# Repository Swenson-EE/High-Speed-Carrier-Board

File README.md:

# LattePanda-Mu High-Speed Carrier Board

A custom carrier board designed for the **LattePanda Mu** compute module, with a focus on high-speed digital design, signal integrity, power distribution, and practical PCB design.

This project was developed to apply high-speed PCB design concepts to a real embedded computing platform. The design process incorporated concepts studied through online courses, technical forums, datasheets, and reference designs.

> **Project Status:** Fabrication
> **PCB Design Tool:** KiCad
> **Primary Focus:** High-speed digital design, power distribution, signal integrity, and embedded hardware

---

## Overview

The goal of this project is to design a custom carrier board around the LattePanda Mu rather than relying on an off-the-shelf carrier board to explore high-speed digital design concepts.

The carrier board is intended to provide practical interfaces for development and experimentation while giving me experience designing a PCB containing multiple high-speed interfaces.

### Design Goals

- Develop a custom carrier board for the LattePanda Mu
- Apply high-speed PCB layout techniques
- Develop controlled-impedance routing practices
- Maintain appropriate differential-pair geometry
- Minimize high-speed signal discontinuities
- Develop a robust power distribution network
- Practice schematic-to-PCB design workflows
- Use datasheets and reference documentation to make design decisions
- Validate the design using available electrical and PCB design tools
- Produce a board suitable for fabrication and bring-up

---

## Hardware

### Compute Module

**LattePanda Mu**

The LattePanda Mu provides the primary compute platform for the carrier board.

The carrier board interfaces with the module through its high-density connectors and routes the available interfaces to the desired peripherals and connectors.

---

## PCB Designs

<table style="background: white;">
  <tr>
    <td align="center"><b>Top Silk Screen</b><br></td>
  </tr>
  <tr>
    <td align="center"><b>Front Cu (L1)</b><br></td>
  </tr>
  <tr>
    <td align="center"><b>GND (L2)</b><br></td>
  </tr>
  <tr>
    <td align="center"><b>PWR (L3)</b><br></td>
  </tr>
  <tr>
    <td align="center"><b>Bottom Cu (L4)</b><br></td>
  </tr>
</table>

## Interfaces

The carrier board is designed around several interfaces provided by the LattePanda Mu.

| Interface      | Purpose                     | Design Considerations                       |
| -------------- | --------------------------- | ------------------------------------------- |
| USB            | Peripheral connectivity     | High-speed differential routing             |
| HDMI / Display | Display output              | Differential high-speed routing             |
| Ethernet       | Network connectivity        | Differential pairs and magnetics            |
| PCIe           | Expansion                   | Controlled impedance / differential routing |
| M.2            | Expansion/storage           | High-speed differential routing             |
| GPIO           | General-purpose I/O         | Digital signal integrity                    |
| Power          | Module and peripheral power | Power integrity / decoupling                |

---

# High-Speed PCB Design

A major purpose of this project is to practice PCB design techniques applicable to high-speed digital hardware.

Rather than treating PCB traces simply as electrical connections, the design considers them as transmission lines at sufficiently high signal frequencies.

Areas being considered include:

### Controlled Impedance

High-speed interfaces are routed using appropriate controlled-impedance structures based on the PCB stackup and manufacturer's capabilities.

Examples include:

- Differential impedance
- Single-ended impedance
- Trace width
- Trace spacing
- Reference planes
- Dielectric thickness
- Copper thickness

The final trace geometries are based on the selected PCB stackup rather than relying solely on generic routing rules.

### Differential Pairs

High-speed differential interfaces are routed as matched differential pairs where required.

Design considerations include:

- Differential impedance
- Pair spacing
- Intra-pair length matching
- Continuous reference planes
- Avoiding unnecessary vias
- Minimizing discontinuities
- Maintaining consistent routing geometry

### Return Paths

High-speed signal routing considers the return current path rather than treating the signal trace independently.

Particular attention is given to:

- Continuous reference planes
- Plane transitions
- Ground vias
- Layer transitions
- Signal crossings
- Connector transitions

### Via Design

Vias can introduce discontinuities into high-speed signals.

Where applicable, the design considers:

- Via stubs
- Via placement
- Differential via geometry
- Ground-via placement
- Layer transitions
- Back-drilling requirements

---

# Power Distribution

The carrier board includes power regulation and distribution for the compute module and attached peripherals.

Power design considerations include:

- Input power requirements
- Voltage regulation
- Current requirements
- Decoupling
- Ground-plane design

Decoupling capacitors are placed with consideration for the physical connection between the capacitor, power pin, and return path rather than simply placing them near the associated component.

---

# PCB Stackup

The PCB stackup is an important part of the high-speed design.

The stackup is selected based on the requirements of the interfaces being routed and the capabilities of the intended PCB manufacturer.

Example stackup:

| Layer | Function |
| ----- | -------- |
| L1    | Signal   |
| L2    | Ground   |
| L3    | Power    |
| L4    | Signal   |

The stackup is used to determine the appropriate controlled-impedance trace geometries.

---

# Research & Learning

This project is also a practical study of high-speed PCB design.

The design process has been informed by:

- LattePanda Mu documentation
- Component datasheets
- Manufacturer application notes
- PCB fabrication guidelines
- High-speed PCB design coursework
- Engineering forums
- Technical discussions
- Reference designs
- Signal-integrity design practices

The purpose of using these resources is to understand **why** particular PCB design decisions are made rather than simply reproducing an existing board.

Where external designs or reference material influence the project, the relevant source will be documented in the project documentation.

---

# Verification

Before fabrication, the design will be reviewed using:

- Electrical rule checking
- PCB design rule checking
- Connectivity verification
- Differential-pair constraints
- Length matching constraints
- Controlled-impedance calculations
- Power-tree review
- Datasheet requirement verification
- Manufacturer design-rule review

Where practical, calculations and design assumptions will be documented in the `/docs` directory.

---

# Disclaimer

This is an independent educational hardware project.

The project is intended to demonstrate my understanding and application of PCB design principles. It is not an official LattePanda design.

The design should be independently reviewed and validated before being used in a production or safety-critical application.

---

# References

- LattePanda Mu documentation
- LattePanda Mu hardware/reference documentation
- Relevant component datasheets
- PCB manufacturer fabrication specifications
- High-speed PCB design course material
- Relevant application notes and technical references

---

## Author

**Tyler Swenson**

This project was created as a hands-on embedded hardware and high-speed PCB design project, with an emphasis on understanding the engineering decisions behind the design rather than simply producing a functioning PCB.

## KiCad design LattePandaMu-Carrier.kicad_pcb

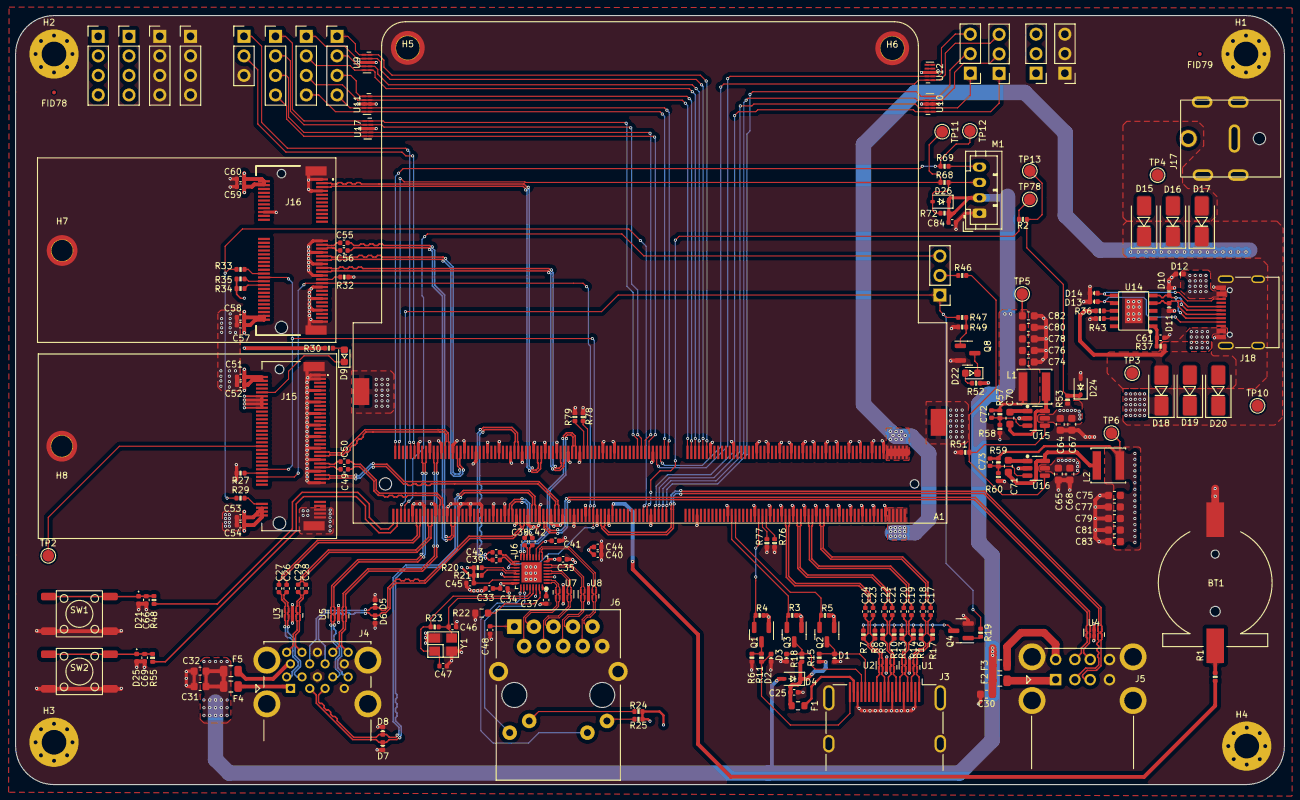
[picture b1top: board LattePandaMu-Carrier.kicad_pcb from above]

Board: 4 copper layers, 165.0 x 100.0 mm, 218 parts (0 on the bottom side), 174 nets.

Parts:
A1: LattePanda_Mu; LattePanda_Module_H8.0mm_Horizontal
BT1: Battery_Cell; Battery_Holder_CR1220_S8411-45R
C17, C18, C19, C20, C21, C22, C23, C24, C25, C26, C27, C28, C29, C33, C34, C35, C37, C38, C39, C40, C41, C42, C43, C45, C48, C52, C54, C58, C60, C84: 100nF/50V; C_0402_1005Metric
C30, C31, C32, C64, C65, C67, C68, C74, C75, C76, C77, C80, C81, C82, C83: 22uF/10V; C_0603_1608Metric
C44: 10uF/50V; C_0402_1005Metric
C46, C47, C72, C73: 12pF/50V; C_0402_1005Metric
C49, C50, C55, C56: 220nF/50V; C_0402_1005Metric
C51, C53, C57, C59: 10uF/10V; C_0402_1005Metric
C61, C66, C69: 1uF/16V; C_0402_1005Metric
C70, C71, C78, C79: 100nF/50V; C_0603_1608Metric
D1, D2, D3, D5, D6, D7, D8: ESD5V0B03; D_0402_1005Metric
D4, D26: 1N5819WS; D_SOD-323
D9: LED_G; LED_0603_1608Metric
D10, D11, D21, D25: ESD9B5.0ST5G; D_0402_1005Metric
D12, D13, D14: D_Zener; D_0402_1005Metric
D15, D16, D17, D18, D19, D20: D_Schottky; D_SMA
D22: LED; LED_0603_1608Metric
D24: 3V3 Izt=5mA; D_SOD-323
F1: 6V/50mA; R_0603_1608Metric
F2, F3, F4, F5: 6V/1A; Fuse_0805_2012Metric
FID78, FID79: Fiducial; Fiducial_0.5mm_Mask1mm
H1, H2, H3, H4: MountingHole_Pad; MountingHole_3.2mm_M3_Pad_Via
H5, H6: MountingHole_Pad; MountingHole_3mm_M2_Pad_TopOnly
H7, H8: MountingHole_M2.0; MountingHole_2.7mm_M2_Pad_TopOnly
J1, J8, J10, J11, J14: Conn_01x03_Pin; PinHeader_1x03_P2.54mm_Vertical
J3: HDMI_A; HDMI_A_Molex_208658-1001_Horizontal
J4: USB3_A_Stacked; USB3_A_Molex_48406-0001_Horizontal_Stacked
J5: USB_A_Stacked; USB_A_CUI_UJ2-ADH-TH_Horizontal_Stacked
J6: RJ45_RB1-125B8G1A; RJ45_UDE_RB1-125B8G1A
J7, J9, J12, J13, J19, J20, J21: Conn_01x04_Pin; PinHeader_1x04_P2.54mm_Vertical
J15: Bus_M.2_Socket_M; PCIe_M.2_Connectors_P=0.5mm_H=4.2mm_KeyM
J16: Bus_M.2_Socket_E; PCIe_M.2_Connectors_P=0.5mm_H=4.2mm_KeyE
J17: Barrel_Jack_Switch; DC_Jack_DC007B_30V_10A
J18: USB_C_Receptacle_USB2.0_16P; USB_C_Receptacle_G-Switch_GT-USB-7010ASV
JP1: Jumper_3_Bridged12; PinHeader_1x03_P2.54mm_Vertical
L1, L2: 2.2uH/4.3A; L_Sunlord_SWPA4020S
M1: Fan_4pin; JST_PH_B4B-PH-K_1x04_P2.00mm_Vertical
Q1, Q2, Q3, Q4: 2SK3018; SOT-23
Q8: 2N7002; SOT-23
R1, R11, R37, R47: 1k/1%; R_0402_1005Metric
R2, R20, R21, R34, R35, R36, R49, R58, R78, R79: 10k/1%; R_0402_1005Metric
R3, R5, R15, R18, R19, R52, R53: 2.2k/1%; R_0402_1005Metric
R4, R23: 1M/1%; R_0402_1005Metric
R6, R59, R68: 21.5k/1%; R_0402_1005Metric
R7, R8, R9, R10, R13, R14, R16, R17, R24, R25: 470R/1%; R_0402_1005Metric
R22: 2.49k/1%; R_0603_1608Metric
R27, R29, R32, R33: 0R/1%; R_0402_1005Metric
R30: 2.2K/1%; R_0402_1005Metric
R43: 56k/1%; R_0402_1005Metric
R46, R51, R76, R77: 100k/1%; R_0402_1005Metric
R48, R55, R69: 100R/1%; R_0402_1005Metric
R57: 75k/1%; R_0402_1005Metric
R60, R72: 4.7k/1%; R_0402_1005Metric
SW1, SW2: SW_Push; SW_Push_6x6x6
TP2, TP3, TP4, TP5, TP6, TP10, TP11, TP12, TP13, TP78: TestPoint; TestPoint_Pad_D1.5mm
U1, U2, U3, U4, U5: D3V3XA4B10LP; Diodes_UDFN-10_1.0x2.5mm_P0.5mm
U6: RTL8111H-CG-RH; QFN-32-1EP_4x4mm_P0.4mm_EP2.65x2.65mm
U7, U8, U9, U10, U11, U12, U17: ULC0524P; Diodes_UDFN-10_1.0x2.5mm_P0.5mm
U14: USB PD等快充协议受电芯片-CH224K-ESSOP10; ESSOP-10-1EP_3.9x5mm_P1.0mm_EP3.2x2.3
U15, U16: LM2734X; TSOT-23-6
Y1: 25MHz; Crystal_SMD_3225-4Pin_3.2x2.5mm

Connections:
5V_HDMI_VCC: C25.1, D4.1 (K), F1.1, R15.2, R18.2
+1V0: C33.2, C34.2, C35.2, C40.2, C44.2, U6.3 (AVDD10), U6.8 (AVDD10), U6.22 (DVDD10), U6.24 (REGOUT), U6.30 (AVDD10)
+3.3V: C37.2, C41.2, C45.2, C51.1, C52.1, C53.1, C54.1, C57.1, C58.1, C59.1, C60.1, C73.1, C75.1, C77.1, C79.1, C81.1, C83.1, J13.1, J13.2, J13.3, J13.4, J14.1, J14.2, J14.3, J15.2 (3.3V), J15.4 (3.3V), J15.12 (3.3V), J15.14 (3.3V), J15.16 (3.3V), J15.18 (3.3V), J15.70 (3.3V), J15.72 (3.3V), J15.74 (3.3V), J16.2 (3.3V), J16.4 (3.3V), J16.72 (3.3V), J16.74 (3.3V), J21.1, J21.2, J21.3, J21.4, L2.2, Q1.1 (G), Q2.1 (G), Q3.1 (G), R3.2, R4.2, R5.2, R20.2, R21.2, R24.2, R25.2, R30.2, R34.2, R35.2, R52.2, R59.2, TP6.1 (1_1), U6.11 (AVDD33), U6.23 (VDDREG), U6.32 (AVDD33)
+5V: C30.2, C31.2, C32.2, C72.1, C74.1, C76.1, C78.1, C80.1, C82.1, C84.1, D4.2 (A), D26.1 (K), F2.1, F3.1, F4.1, F5.1, L1.2, M1.2 (+), R57.2, R72.1, TP5.1 (1_1)
+12V: D15.2 (A), D16.2 (A), D17.2 (A), J17.1, TP4.1 (1_1)
+15V: D12.1 (K), D18.2 (A), D19.2 (A), D20.2 (A), J18.A4 (VBUS), J18.A9 (VBUS), J18.B4 (VBUS), J18.B9 (VBUS), R36.1, R37.1, TP3.1 (1_1)
+BATT: A1.115 (VBAT), R1.2
/Fan/FAN_1_PWM: A1.2 (FAN1_PWM), R69.1, TP12.1 (1_1)
/Fan/FAN_1_TAC: A1.4 (FAN1_TAC), R68.1, TP11.1 (1_1)
/GPIO/GPP_D0: A1.128 (GPP_D0), J19.1, U17.1, U17.10 (NC)
/GPIO/GPP_D1: A1.130 (GPP_D1), J19.2, U17.2, U17.9 (NC)
/GPIO/GPP_D2: A1.132 (GPP_D2), J19.3, U17.4, U17.7 (NC)
/GPIO/GPP_D3: A1.134 (GPP_D3), J19.4, U17.5, U17.6 (NC)
/GPIO/I2C2_SCL: A1.154 (I2C2_SCL), J9.1, U9.2, U9.9 (NC)
/GPIO/I2C2_SDA: A1.156 (I2C2_SDA), J7.1, U9.1, U9.10 (NC)
/GPIO/I2C3_SCL: A1.150 (I2C3_SCL), J9.2, U9.5, U9.6 (NC)
/GPIO/I2C3_SDA: A1.152 (I2C3_SDA), J7.2, U9.4, U9.7 (NC)
/GPIO/I2C4_SCL: A1.146 (I2C4_SCL), J9.3, U11.2, U11.9 (NC)
/GPIO/I2C4_SDA: A1.148 (I2C4_SDA), J7.3, U11.1, U11.10 (NC)
/GPIO/I2C5_SCL: A1.142 (I2C5_SCL), J9.4, U11.5, U11.6 (NC)
/GPIO/I2C5_SDA: A1.144 (I2C5_SDA), J7.4, U11.4, U11.7 (NC)
/GPIO/SOC_UART0_RX: A1.137 (UART0_RXD), J8.1, U10.1, U10.10 (NC)
/GPIO/SOC_UART0_TX: A1.139 (UART0_TXD), J10.1, U10.2, U10.9 (NC)
/GPIO/SOC_UART1_RX: A1.141 (UART1_RXD), J8.2, U10.4, U10.7 (NC)
/GPIO/SOC_UART1_TX: A1.143 (UART1_TXD), J10.2, U10.5, U10.6 (NC)
/GPIO/SOC_UART2_RX: A1.140 (UART2_RXD), J8.3, U12.1, U12.10 (NC)
/GPIO/SOC_UART2_TX: A1.138 (UART2_TXD), J10.3, U12.2, U12.9 (NC)
/Gigabit Ethernet/GbE_PCIe_CLK+: A1.94 (REFCLK4+), U6.15 (REFCLK_P)
/Gigabit Ethernet/GbE_PCIe_CLK-: A1.96 (REFCLK4-), U6.16 (REFCLK_N)
/Gigabit Ethernet/GbE_PCIe_RX+: A1.64 (HSIO6_RX+), C43.1
/Gigabit Ethernet/GbE_PCIe_RX-: A1.66 (HSIO6_RX-), C39.1
/Gigabit Ethernet/GbE_PCIe_TX+: A1.61 (HSIO6_TX+), C42.1
/Gigabit Ethernet/GbE_PCIe_TX-: A1.63 (HSIO6_TX-), C38.1
/Gigabit Ethernet/HSI+: C42.2, U6.13 (HSIP)
/Gigabit Ethernet/HSI-: C38.2, U6.14 (HSIN)
/Gigabit Ethernet/HSO+: C43.2, U6.17 (HSOP)
/Gigabit Ethernet/HSO-: C39.2, U6.18 (HSON)
/Gigabit Ethernet/LED1_1000: J6.L4, U6.26 (LED1)
/Gigabit Ethernet/LED2_ACT: J6.L2, U6.25 (LED2)
/Gigabit Ethernet/MDI0+: J6.R2 (TD1+), U6.1 (MDIP0), U7.1, U7.10 (NC)
/Gigabit Ethernet/MDI0-: J6.R3 (TD1-), U6.2 (MDIN0), U7.2, U7.9 (NC)
/Gigabit Ethernet/MDI1+: J6.R4 (TD2+), U6.4 (MDIP1), U7.4, U7.7 (NC)
/Gigabit Ethernet/MDI1-: J6.R5 (TD2-), U6.5 (MDIN1), U7.5, U7.6 (NC)
/Gigabit Ethernet/MDI2+: J6.R6 (TD3+), U6.6 (MDIP2), U8.5, U8.6 (NC)
/Gigabit Ethernet/MDI2-: J6.R7 (TD3-), U6.7 (MDIN2), U8.4, U8.7 (NC)
/Gigabit Ethernet/MDI3+: J6.R8 (TD4+), U6.9 (MDIP3), U8.2, U8.9 (NC)
/Gigabit Ethernet/MDI3-: J6.R9 (TD4-), U6.10 (MDIN3), U8.1, U8.10 (NC)
/HDMI/DDC_SCL: D1.2 (A2), J3.15 (SCL), Q2.3 (D), R15.1
/HDMI/DDC_SDA: D3.2 (A2), J3.16 (SDA), Q3.3 (D), R18.1
/HDMI/DDI_B_DDC_SCL: A1.171 (DDIB_DDC_SCL), Q2.2 (S), R5.1
/HDMI/DDI_B_DDC_SDA: A1.169 (DDIB_DDC_SDA), Q3.2 (S), R3.1
/HDMI/DDI_B_HPD: A1.183 (DDIB_HPD), Q1.2 (S), R4.1
/HDMI/DDI_B_TX0+: A1.217 (DDIB_TX0+), C17.1
/HDMI/DDI_B_TX0-: A1.215 (DDIB_TX0-), C18.1
/HDMI/DDI_B_TX1+: A1.211 (DDIB_TX1+), C19.1
/HDMI/DDI_B_TX1-: A1.209 (DDIB_TX1-), C20.1
/HDMI/DDI_B_TX2+: A1.205 (DDIB_TX2+), C21.1
/HDMI/DDI_B_TX2-: A1.203 (DDIB_TX2-), C22.1
/HDMI/DDI_B_TX3+: A1.199 (DDIB_TX3+), C23.1
/HDMI/DDI_B_TX3-: A1.197 (DDIB_TX3-), C24.1
/HDMI/HPD: D2.2 (A2), J3.19 (HPD), R11.1
/HDMI/TMDS_CK+: C23.2, J3.10 (CK+), R8.2, U2.4, U2.7 (NC)
/HDMI/TMDS_CK-: C24.2, J3.12 (CK-), R7.2, U2.5, U2.6 (NC)
/HDMI/TMDS_D0+: C21.2, J3.7 (D0+), R10.2, U2.1, U2.10 (NC)
/HDMI/TMDS_D0-: C22.2, J3.9 (D0-), R9.2, U2.2, U2.9 (NC)
/HDMI/TMDS_D1+: C19.2, J3.4 (D1+), R14.2, U1.4, U1.7 (NC)
/HDMI/TMDS_D1-: C20.2, J3.6 (D1-), R13.2, U1.5, U1.6 (NC)
/HDMI/TMDS_D2+: C17.2, J3.1 (D2+), R17.2, U1.1, U1.10 (NC)
/HDMI/TMDS_D2-: C18.2, J3.3 (D2-), R16.2, U1.2, U1.9 (NC)
/LattePanda Module/HSIO_0_TX+: A1.13 (HSIO0_TX+), C27.1
/LattePanda Module/HSIO_0_TX-: A1.15 (HSIO0_TX-), C26.1
/LattePanda Module/HSIO_1_TX+: A1.19 (HSIO1_TX+), C29.1
/LattePanda Module/HSIO_1_TX-: A1.21 (HSIO1_TX-), C28.1
/LattePanda Module/HSIO_2_RX+: A1.28 (HSIO2_RX+), J15.43 (PERp0/SATA-B-)
/LattePanda Module/HSIO_2_RX-: A1.30 (HSIO2_RX-), J15.41 (PERn0/SATA-B+)
/LattePanda Module/HSIO_2_TX+: A1.25 (HSIO2_TX+), C49.1
/LattePanda Module/HSIO_2_TX-: A1.27 (HSIO2_TX-), C50.1
/LattePanda Module/HSIO_3_RX+: A1.34 (HSIO3_RX+), J16.41 (PERp0)
/LattePanda Module/HSIO_3_RX-: A1.36 (HSIO3_RX-), J16.43 (PERn0)
/LattePanda Module/HSIO_3_TX+: A1.31 (HSIO3_TX+), C55.1
/LattePanda Module/HSIO_3_TX-: A1.33 (HSIO3_TX-), C56.1
/LattePanda Module/REFCLK_0+: A1.85 (REFCLK0+), J15.55 (REFCLKp)
/LattePanda Module/REFCLK_0-: A1.87 (REFCLK0-), J15.53 (REFCLKn)
/LattePanda Module/REFCLK_3+: A1.88 (REFCLK3+), J16.47 (REFCLKp0)
/LattePanda Module/REFCLK_3-: A1.90 (REFCLK3-), J16.49 (REFCLKn0)
/LattePanda Module/SLS_S3: A1.7 (SLS_S3), JP1.3 (B)
/LattePanda Module/SUSCLK_WIFI: A1.131 (SUSCLK), R29.2, R33.2
/LattePanda Module/USB_2_P7+: A1.76 (USB2_P7+), J16.3 (USB_D+)
/LattePanda Module/USB_2_P7-: A1.78 (USB2_P7-), J16.5 (USB_D-)
/LattePanda Module/~PWR_SW: A1.1 (~PWRBTN), R48.1
/LattePanda Module/~RST_SW: A1.3 (~RSTBTN), R55.1
/M.2 M Key/CON_PCIE_TX1+: C49.2, J15.49 (PETp0/SATA-A+)
/M.2 M Key/CON_PCIE_TX1-: C50.2, J15.47 (PETn0/SATA-A-)
/M.2 M Key/CON_PCIE_TX_0+: C55.2, J16.35 (PETp0)
/M.2 M Key/CON_PCIE_TX_0-: C56.2, J16.37 (PETn0)
/M.2 M Key/~CLKREQE: J16.53 (~CLKREQ0), R32.1
/M.2 M Key/~CLKREQM: J15.52 (~CLKREQ), R27.1
/Power Supply/CC1: D13.1 (K), J18.A5 (CC1), U14.7 (CC1)
/Power Supply/CC2: D14.1 (K), J18.B5 (CC2), U14.6 (CC2)
/Power Supply/PWR_C_D+: D11.2 (A2), J18.A6 (D+), J18.B6 (D+), U14.4 (DP)
/Power Supply/PWR_C_D-: D10.2 (A2), J18.A7 (D-), J18.B7 (D-), U14.5 (DM)
/Power Supply/PWR_EN: R46.2, R51.2, U15.4 (EN), U16.4 (EN)
/USB 2.0 & 3.0/CON_USB1_D_N: A1.109 (USB2_P5-), J5.2 (D1-), U4.2, U4.9 (NC)
/USB 2.0 & 3.0/CON_USB1_D_P: A1.111 (USB2_P5+), J5.3 (D1+), U4.1, U4.10 (NC)
/USB 2.0 & 3.0/CON_USB2_D_N: A1.79 (USB2_P3-), J5.6 (D2-), U4.5, U4.6 (NC)
/USB 2.0 & 3.0/CON_USB2_D_P: A1.81 (USB2_P3+), J5.7 (D2+), U4.4, U4.7 (NC)
/USB 2.0 & 3.0/CON_USB3_D_N: A1.73 (USB2_P2-), D8.1 (A1), J4.2 (D1-)
/USB 2.0 & 3.0/CON_USB3_D_P: A1.75 (USB2_P2+), D7.1 (A1), J4.3 (D1+)
/USB 2.0 & 3.0/CON_USB3_SSRX_N: A1.18 (HSIO0_RX-), J4.5 (SSRX1-), U5.4, U5.7 (NC)
/USB 2.0 & 3.0/CON_USB3_SSRX_P: A1.16 (HSIO0_RX+), J4.6 (SSRX1+), U5.5, U5.6 (NC)
/USB 2.0 & 3.0/CON_USB3_SSTX_N: C26.2, J4.8 (SSTX1-), U3.4, U3.7 (NC)
/USB 2.0 & 3.0/CON_USB3_SSTX_P: C27.2, J4.9 (SSTX1+), U3.5, U3.6 (NC)
/USB 2.0 & 3.0/CON_USB4_D_N: A1.67 (USB2_P1-), D6.1 (A1), J4.11 (D2-)
/USB 2.0 & 3.0/CON_USB4_D_P: A1.69 (USB2_P1+), D5.1 (A1), J4.12 (D2+)
/USB 2.0 & 3.0/CON_USB4_SSRX_N: A1.24 (HSIO1_RX-), J4.14 (SSRX2-), U5.1, U5.10 (NC)
/USB 2.0 & 3.0/CON_USB4_SSRX_P: A1.22 (HSIO1_RX+), J4.15 (SSRX2+), U5.2, U5.9 (NC)
/USB 2.0 & 3.0/CON_USB4_SSTX_N: C28.2, J4.17 (SSTX2-), U3.1, U3.10 (NC)
/USB 2.0 & 3.0/CON_USB4_SSTX_P: C29.2, J4.18 (SSTX2+), U3.2, U3.9 (NC)
/~PEWAKE: A1.103 (~WAKE), J15.54 (~PEWAKE), J16.55 (~PEWAKE0)
/~PLT_RST: A1.105 (~PLTRST), J15.50 (~PERST), J16.52 (~PERST0), U6.19 (PERSTB)
/~PWR_LED/~PSON: A1.5 (SLS_S0), JP1.1 (A), R19.1, R47.1
GND: A1.11 (GND), A1.14 (GND), A1.17 (GND), A1.20 (GND), A1.23 (GND), A1.26 (GND), A1.29 (GND), A1.32 (GND), A1.35 (GND), A1.38 (GND), A1.41 (GND), A1.44 (GND), A1.47 (GND), A1.50 (GND), A1.53 (GND), A1.56 (GND), A1.59 (GND), A1.62 (GND), A1.65 (GND), A1.68 (GND), A1.71 (GND), A1.74 (GND), A1.77 (GND), A1.80 (GND), A1.83 (GND), A1.86 (GND), A1.89 (GND), A1.92 (GND), A1.95 (GND), A1.98 (GND), A1.101 (GND), A1.107 (GND), A1.110 (GND), A1.113 (GND), A1.116 (GND), A1.135 (GND), A1.136 (GND), A1.151 (GND), A1.158 (GND), A1.167 (GND), A1.170 (GND), A1.181 (GND), A1.182 (GND), A1.188 (GND), A1.189 (GND), A1.194 (GND), A1.195 (GND), A1.200 (GND), A1.201 (GND), A1.206 (GND), A1.207 (GND), A1.212 (GND), A1.213 (GND), A1.218 (GND), A1.219 (GND), A1.224 (GND), A1.225 (GND), A1.230 (GND), A1.231 (GND), A1.236 (GND), A1.237 (GND), A1.242 (GND), A1.243 (GND), A1.248 (GND), A1.249 (GND), A1.MP (Mountinge_Pads), BT1.2 (-), C25.2, C30.1, C31.1, C32.1, C33.1, C34.1, C35.1, C37.1, C40.1, C41.1, C44.1, C45.1, C46.2, C47.2, C48.1, C51.2, C52.2, C53.2, C54.2, C57.2, C58.2, C59.2, C60.2, C61.2, C64.2, C65.1, C66.2, C67.2, C68.1, C69.2, C74.2, C75.2, C76.2, C77.2, C78.2, C79.2, C80.2, C81.2, C82.2, C83.2, C84.2, D1.1 (A1), D2.1 (A1), D3.1 (A1), D5.2 (A2), D6.2 (A2), D7.2 (A2), D8.2 (A2), D10.1 (A1), D11.1 (A1), D12.2 (A), D13.2 (A), D14.2 (A), D21.2 (A2), D24.2 (A), D25.2 (A2), H1.1 (1_1), H2.1 (1_1), H3.1 (1_1), H4.1 (1_1), H5.1 (1_1), H6.1 (1_1), H7.1 (1_1), H8.1 (1_1), J1.3, J3.2 (D2S), J3.5 (D1S), J3.8 (D0S), J3.11 (CKS), J3.17 (GND), J3.SH, J4.4 (GND1), J4.7 (DRAIN1), J4.13 (GND2), J4.16 (DRAIN2), J4.19 (SHIELD), J5.4 (GND1), J5.8 (GND2), J5.9 (Shield), J6.R10 (GND), J6.SH, J11.1, J11.2, J11.3, J12.1, J12.2, J12.3, J12.4, J15.1 (GND), J15.3 (GND), J15.9 (GND), J15.15 (GND), J15.21 (GND), J15.27 (GND), J15.33 (GND), J15.39 (GND), J15.45 (GND), J15.51 (GND), J15.57 (GND), J15.71 (GND), J15.73 (GND), J15.75 (GND), J15.MP1, J15.MP2, J16.1 (GND), J16.7 (GND), J16.18 (GND), J16.33 (GND), J16.39 (GND), J16.45 (GND), J16.51 (GND), J16.57 (GND), J16.63 (GND), J16.69 (GND), J16.75 (GND), J16.MP1, J16.MP2, J17.2, J17.3, J18.A1 (GND), J18.A12 (GND), J18.B1 (GND), J18.B12 (GND), J18.S1 (SHIELD), J20.1, J20.2, J20.3, J20.4, M1.1 (-), Q4.2 (S), Q8.2 (S), R6.1, R22.1, R27.2, R32.2, R43.2, R49.1, R51.1, R58.1, R60.1, R76.2, R77.2, R78.1, R79.1, SW1.2, SW2.2, U1.3 (VSS), U1.8 (VSS), U2.3 (VSS), U2.8 (VSS), U3.3 (VSS), U3.8 (VSS), U4.3 (VSS), U4.8 (VSS), U5.3 (VSS), U5.8 (VSS), U6.33 (GND), U7.3 (VSS), U7.8 (VSS), U8.3 (VSS), U8.8 (VSS), U9.3 (VSS), U9.8 (VSS), U10.3 (VSS), U10.8 (VSS), U11.3 (VSS), U11.8 (VSS), U12.3 (VSS), U12.8 (VSS), U14.0 (GND), U15.2 (GND), U16.2 (GND), U17.3 (VSS), U17.8 (VSS), Y1.2 (G), Y1.4 (G)
unnamed: A1.12 (SIO_UART_RX), J1.2
unnamed: A1.10 (SIO_UART_TX), J1.1
unnamed: A1.187 (TCP0_HPD), R76.1
unnamed: A1.185 (TCP1_HPD), R77.1
unnamed: A1.133 (~BIOS_SEL), R2.1, TP78.1 (1_1)
unnamed: A1.100 (~CLKREQ3), R79.2
unnamed: A1.102 (~CLKREQ4), R78.2
unnamed: BT1.1 (+), R1.1
unnamed: D9.2 (A), R30.1
unnamed: D9.1 (K), J15.10 (DAS/~DSS/~LED1)
unnamed: C66.1, D21.1 (A1), R48.2, SW1.1
unnamed: D22.2 (A), R52.1
unnamed: D22.1 (K), Q8.3 (D)
unnamed: C69.1, D25.1 (A1), R55.2, SW2.1
unnamed: D26.2 (A), M1.3 (Tacho), R68.2, R72.2
unnamed: F1.2, J3.18 (+5V)
unnamed: F4.2, J4.1 (VBUS1)
unnamed: F5.2, J4.10 (VBUS2)
unnamed: F2.2, J5.1 (VBUS1)
unnamed: F3.2, J5.5 (VBUS2)
unnamed: C48.2, J6.R1 (CT)
unnamed: J6.L1, R25.1
unnamed: J6.L3, R24.1
unnamed: J15.38 (DEVSLP), TP2.1 (1_1)
unnamed: J15.68 (SUSCLK), R29.1
unnamed: J16.50 (SUSCLK), R33.1
unnamed: J16.56 (~W_DISABLE1), R34.1
unnamed: J16.54 (~W_DISABLE2), R35.1
unnamed: JP1.2 (C), R46.1
unnamed: M1.4 (PWM), R69.2
unnamed: Q1.3 (D), R6.2, R11.2
unnamed: Q4.3 (D), R7.1, R8.1, R9.1, R10.1, R13.1, R14.1, R16.1, R17.1
unnamed: Q4.1 (G), R19.2
unnamed: Q8.1 (G), R47.2, R49.2
unnamed: C47.1, R23.1, U6.28 (CKXTAL1), Y1.1
unnamed: C46.1, R23.2, U6.29 (CKXTAL2), Y1.3
unnamed: R20.1, U6.20 (ISOLATEB)
unnamed: R21.1, U6.21 (LANWAKEB)
unnamed: R22.2, U6.31 (RSET)
unnamed: U12.5, U12.6 (NC)
unnamed: U12.4, U12.7 (NC)
unnamed: R43.1, U14.9 (CFG1)
unnamed: R36.2, U14.8 (VBUS)
unnamed: C61.1, R37.2, U14.1 (VDD)
unnamed: C70.2, U15.1 (BOOST)
unnamed: C72.2, R57.1, R58.2, U15.3 (FB)
unnamed: C70.1, L1.1, U15.6 (SW)
unnamed: C71.2, U16.1 (BOOST)
unnamed: C73.2, R59.1, R60.2, U16.3 (FB)
unnamed: C71.1, L2.1, U16.6 (SW)
VDC: A1.250 (VIN), A1.251 (VIN), A1.252 (VIN), A1.253 (VIN), A1.254 (VIN), A1.255 (VIN), A1.256 (VIN), A1.257 (VIN), A1.258 (VIN), A1.259 (VIN), A1.260 (VIN), C64.1, C65.2, C67.1, C68.2, D15.1 (K), D16.1 (K), D17.1 (K), D18.1 (K), D19.1 (K), D20.1 (K), R53.1, TP10.1 (1_1), U15.5 (VIN), U16.5 (VIN)
VPullup: D24.1 (K), R2.2, R53.2, TP13.1 (1_1)
